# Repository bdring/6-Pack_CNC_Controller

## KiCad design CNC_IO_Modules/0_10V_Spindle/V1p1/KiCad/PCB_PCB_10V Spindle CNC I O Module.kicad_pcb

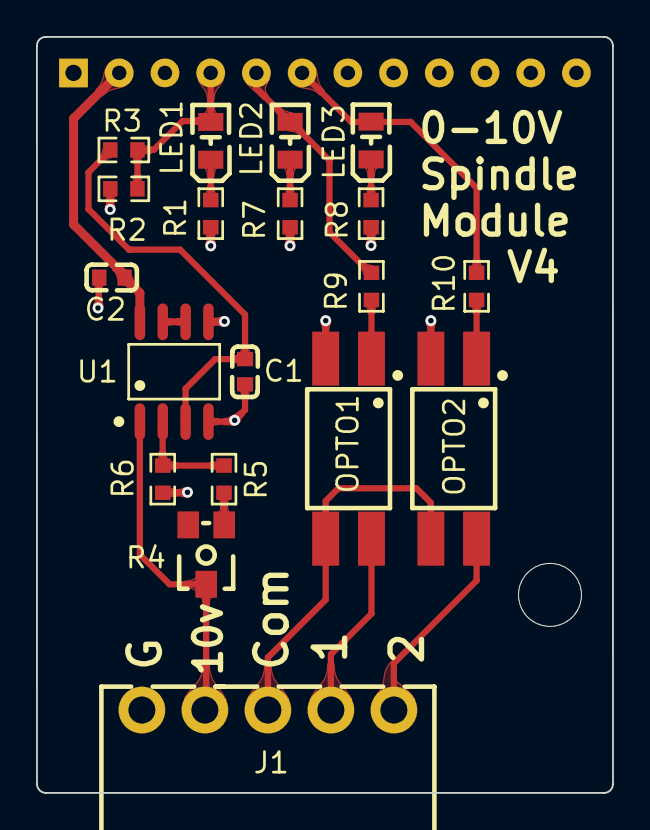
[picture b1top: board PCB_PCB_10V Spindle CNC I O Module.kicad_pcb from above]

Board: 2 copper layers, 32.0 x 42.0 mm, 20 parts (0 on the bottom side), 18 nets.

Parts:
C1, C2: 100nF; C0603
J1: KF2EDGR-3.5-5P; CONN-TH_5P-P3.50_KF2EDGR-3.5-5P
LED1, LED2, LED3: SZYY0805G; LED0805-R-RD
MOD1: 6 Pack Module Pins Bottom; 6 PACK MODULE PCB BOTTOM
OPTO1, OPTO2: EL817S1(C)(TU)-F; OPTO-SMD-4_L4.6-W6.5-P2.54-LS10.3-TL
R1, R7, R8: 2kΩ; R0603
R2, R3, R6: 10kΩ; R0603
R4: 20kΩ; RES-ADJ-SMD_VG039NCH
R5: 4.99kΩ; R0603
R9, R10: 300Ω; R0603
U1: LM358ADT; SOIC-8_L4.9-W3.9-P1.27-LS6.0-BL

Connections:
0_10V_OUT: J1.2, R4.2, U1.1
GND: C1.1, C2.1, J1.1, MOD1.1, MOD1.12, OPTO1.2, OPTO2.2, R1.1, R2.1, R6.1, R7.1, R8.1, U1.4, U1.5
OPTO1_1: OPTO1.1, R9.2
OPTO1_3: J1.3, OPTO1.3, OPTO2.3
OPTO1_4: J1.4, OPTO1.4
OPTO2_4: J1.5, OPTO2.4
OUT1: LED2.1, MOD1.5, R9.1
OUT2: LED3.1, MOD1.6, R10.1
R1_2: LED1.2, R1.2
R4_1: R4.1, R5.2
R7_2: LED2.2, R7.2
R8_2: LED3.2, R8.2
R10_2: OPTO2.1, R10.2
SPINDLE: LED1.1, MOD1.4, R2.2, R3.1
U1_2: R5.1, R6.2, U1.2
U1_3: C1.2, R3.2, U1.3
U1_6: U1.6, U1.7
VMOT: C2.2, MOD1.2, U1.8
